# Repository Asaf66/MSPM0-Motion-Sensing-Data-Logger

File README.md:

# MSPM0 Motion-Sensing & Data-Logger Platform

### Project Overview
A compact, high-performance embedded system designed for precise motion tracking and data acquisition, built around the Texas Instruments MSPM0 series MCU.

### Technical Highlights
* Full PCB Design: Handled the entire process from schematic to layout, focusing on stable power delivery (LDO) and signal routing.
* Embedded Hardware: Integrated a TI MSPM0 series MCU, including USB-C connectivity and a USB-to-UART bridge for easy data logging.
* Sensor Integration: Implemented I2C communication for motion tracking (accelerometer) and managed various digital/analog interfaces like ADC and SPI.

### Visuals

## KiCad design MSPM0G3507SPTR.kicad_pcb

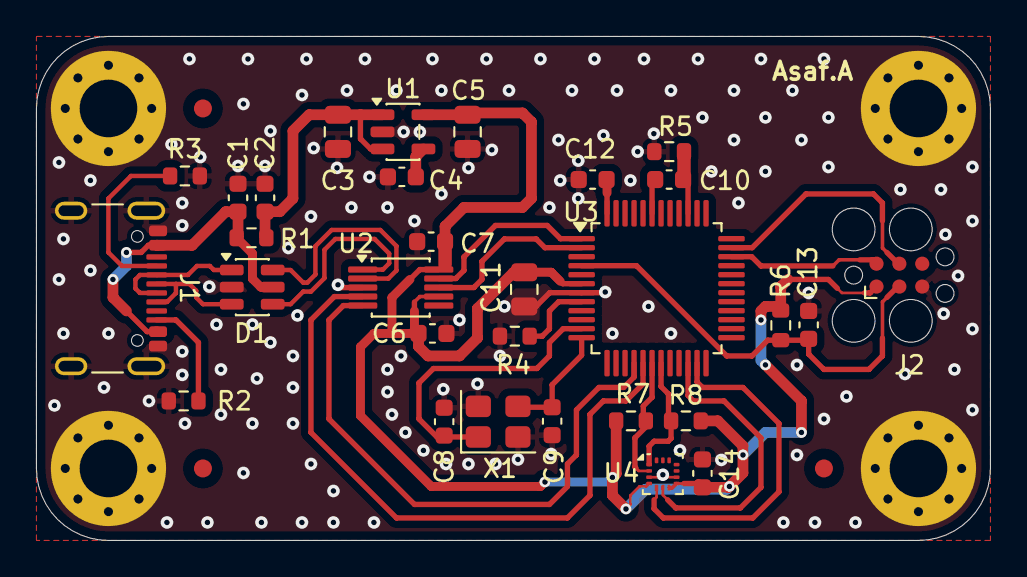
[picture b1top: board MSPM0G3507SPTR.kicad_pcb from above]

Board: 2 copper layers, 53.0 x 28.0 mm, 37 parts (0 on the bottom side), 28 nets.

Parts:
C1, C2, C4, C6, C7, C10, C12, C13, C14: 470n; C_0603_1608Metric
C3, C5, C11: 10u; C_0805_2012Metric
C8, C9: 15p; C_0603_1608Metric
D1: USBLC6-2SC6; SOT-23-6
FID1, FID2, FID3: Fiducial; Fiducial_1mm_Mask2mm
J1: USB_C_Receptacle_USB2.0_16P; USB_C_Receptacle_GCT_USB4105-xx-A_16P_TopMnt_Horizontal
J2: Conn_ARM_SWD_TagConnect_TC2030; Tag-Connect_TC2030-IDC-FP_2x03_P1.27mm_Vertical
MH1, MH2, MH3, MH4: M3; MountingHole_3.2mm_M3_Pad_Via
R1, R5: 0R; R_0603_1608Metric
R2, R3, R6, R7, R8: 5K1; R_0603_1608Metric
R4: 100K; R_0603_1608Metric
U1: SPX3819M5-L-3-3; SOT-23-5
U2: CH340E; MSOP-10_3x3mm_P0.5mm
U3: MSPM0G3507SPTR; LQFP-48_7x7mm_P0.5mm
U4: LIS2DH; LGA-14_2x2mm_P0.35mm_LayoutBorder3x4y
X1: 8MHz; Crystal_SMD_3225-4Pin_3.2x2.5mm

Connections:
+1V35: C12.1, U3.48 (VCORE)
+3V3: C5.1, C6.1, C7.1, C11.1, C14.1, J2.1 (VCC), R6.2, R7.2, R8.2, U1.5 (OUT), U2.7 (VCC), U2.10 (V3), U3.6 (VDD), U4.4 (~CS), U4.7 (Vdd_IO), U4.8 (Vdd)
+VBUS: C1.1, D1.5 (VBUS), J1.A4 (VBUS), J1.A9 (VBUS), J1.B4 (VBUS), J1.B9 (VBUS), R1.1
+VBUSF: C2.1, C3.1, R1.2, U1.1 (IN), U1.3 (EN)
/HFXIN: C8.1, U3.11 (PA5), X1.1
/HFXOUT: C9.1, U3.12 (PA6), X1.3
/NRST: C13.1, J2.3 (~RESET), R6.1, U3.4 (NRST)
/ROSC: R4.1, U3.8 (PA2)
/SWCLK: J2.4 (SWCLK), U3.35 (PA20)
/SWDIO: J2.2 (SWDIO), U3.34 (PA19)
/UARTOCTS: U2.4 (~RTS), U3.17 (PA9)
/UARTORTS: U2.5 (~CTS), U3.16 (PA8)
/UARTRX: U2.8 (TXD), U3.2 (PA1)
/UARTTX: U2.9 (RXD), U3.1 (PA0)
/USBCC1: J1.A5 (CC1), R3.2
/USBCC2: J1.B5 (CC2), R2.2
/USBCD+: D1.3 (I/O2), J1.A6 (D+), J1.B6 (D+)
/USBCD-: D1.1 (I/O1), J1.A7 (D-), J1.B7 (D-)
/USBD+: D1.4 (I/O2), U2.1 (UD+)
/USBD-: D1.6 (I/O1), U2.2 (UD-)
/VREF+: C10.2, U3.43 (PA23)
/VREF-: C10.1, R5.1, U3.39 (PA21)
GND: C1.2, C2.2, C3.2, C4.2, C5.2, C6.2, C7.2, C8.2, C9.2, C11.2, C12.2, C13.2, C14.2, D1.2 (GND), J1.A1 (GND), J1.A12 (GND), J1.B1 (GND), J1.B12 (GND), J1.S1 (SHIELD), J2.5 (GND), MH1.1, MH2.1, MH3.1, MH4.1, R2.1, R3.1, R4.2, R5.2, U1.2 (GND), U2.3 (GND), U3.7 (VSS), U4.3 (SDO), U4.9 (GND), X1.2, X1.4
I2COSCL: R8.1, U3.19 (PA11), U4.1 (SCL/SPC)
I2COSDA: R7.1, U3.18 (PA10), U4.2 (SDA/SDI)
INT1: U3.22 (PB8), U4.6 (INT1)
INT2: U3.23 (PB9), U4.5 (INT2)
unnamed: C4.1, U1.4 (BP)

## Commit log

2026-03-31 Create The MSPM0 Motion-Sensing & Data-Logger
    The MSPM0 Motion-Sensing & Data-Logger Platform is a compact, high-performance embedded system designed for precise motion tracking and data acquisition. Built around the Texas Instruments MSPM0 seri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
2026-03-31 Initialize README with project details
    The MSPM0 Motion-Sensing & Data-Logger Platform is a compact, high-performance embedded system designed for precise motion tracking and data acquisition. Built around the Texas Instruments MSPM0 seri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
2026-03-31 Rename צילום מסך 2026-03-18 183259.png to schematic.png
2026-03-31 Rename צילום מסך 2026-03-18 183422.png to pcb_layout.png
2026-03-31 Rename pcb_layout.png to 3D View.png
2026-03-31 Rename צילום מסך 2026-03-18 183550.png to pcb_layout.png
